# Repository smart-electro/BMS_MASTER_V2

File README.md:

BMS_MASTER_V2
=============

SW and HW for master module of battery management system

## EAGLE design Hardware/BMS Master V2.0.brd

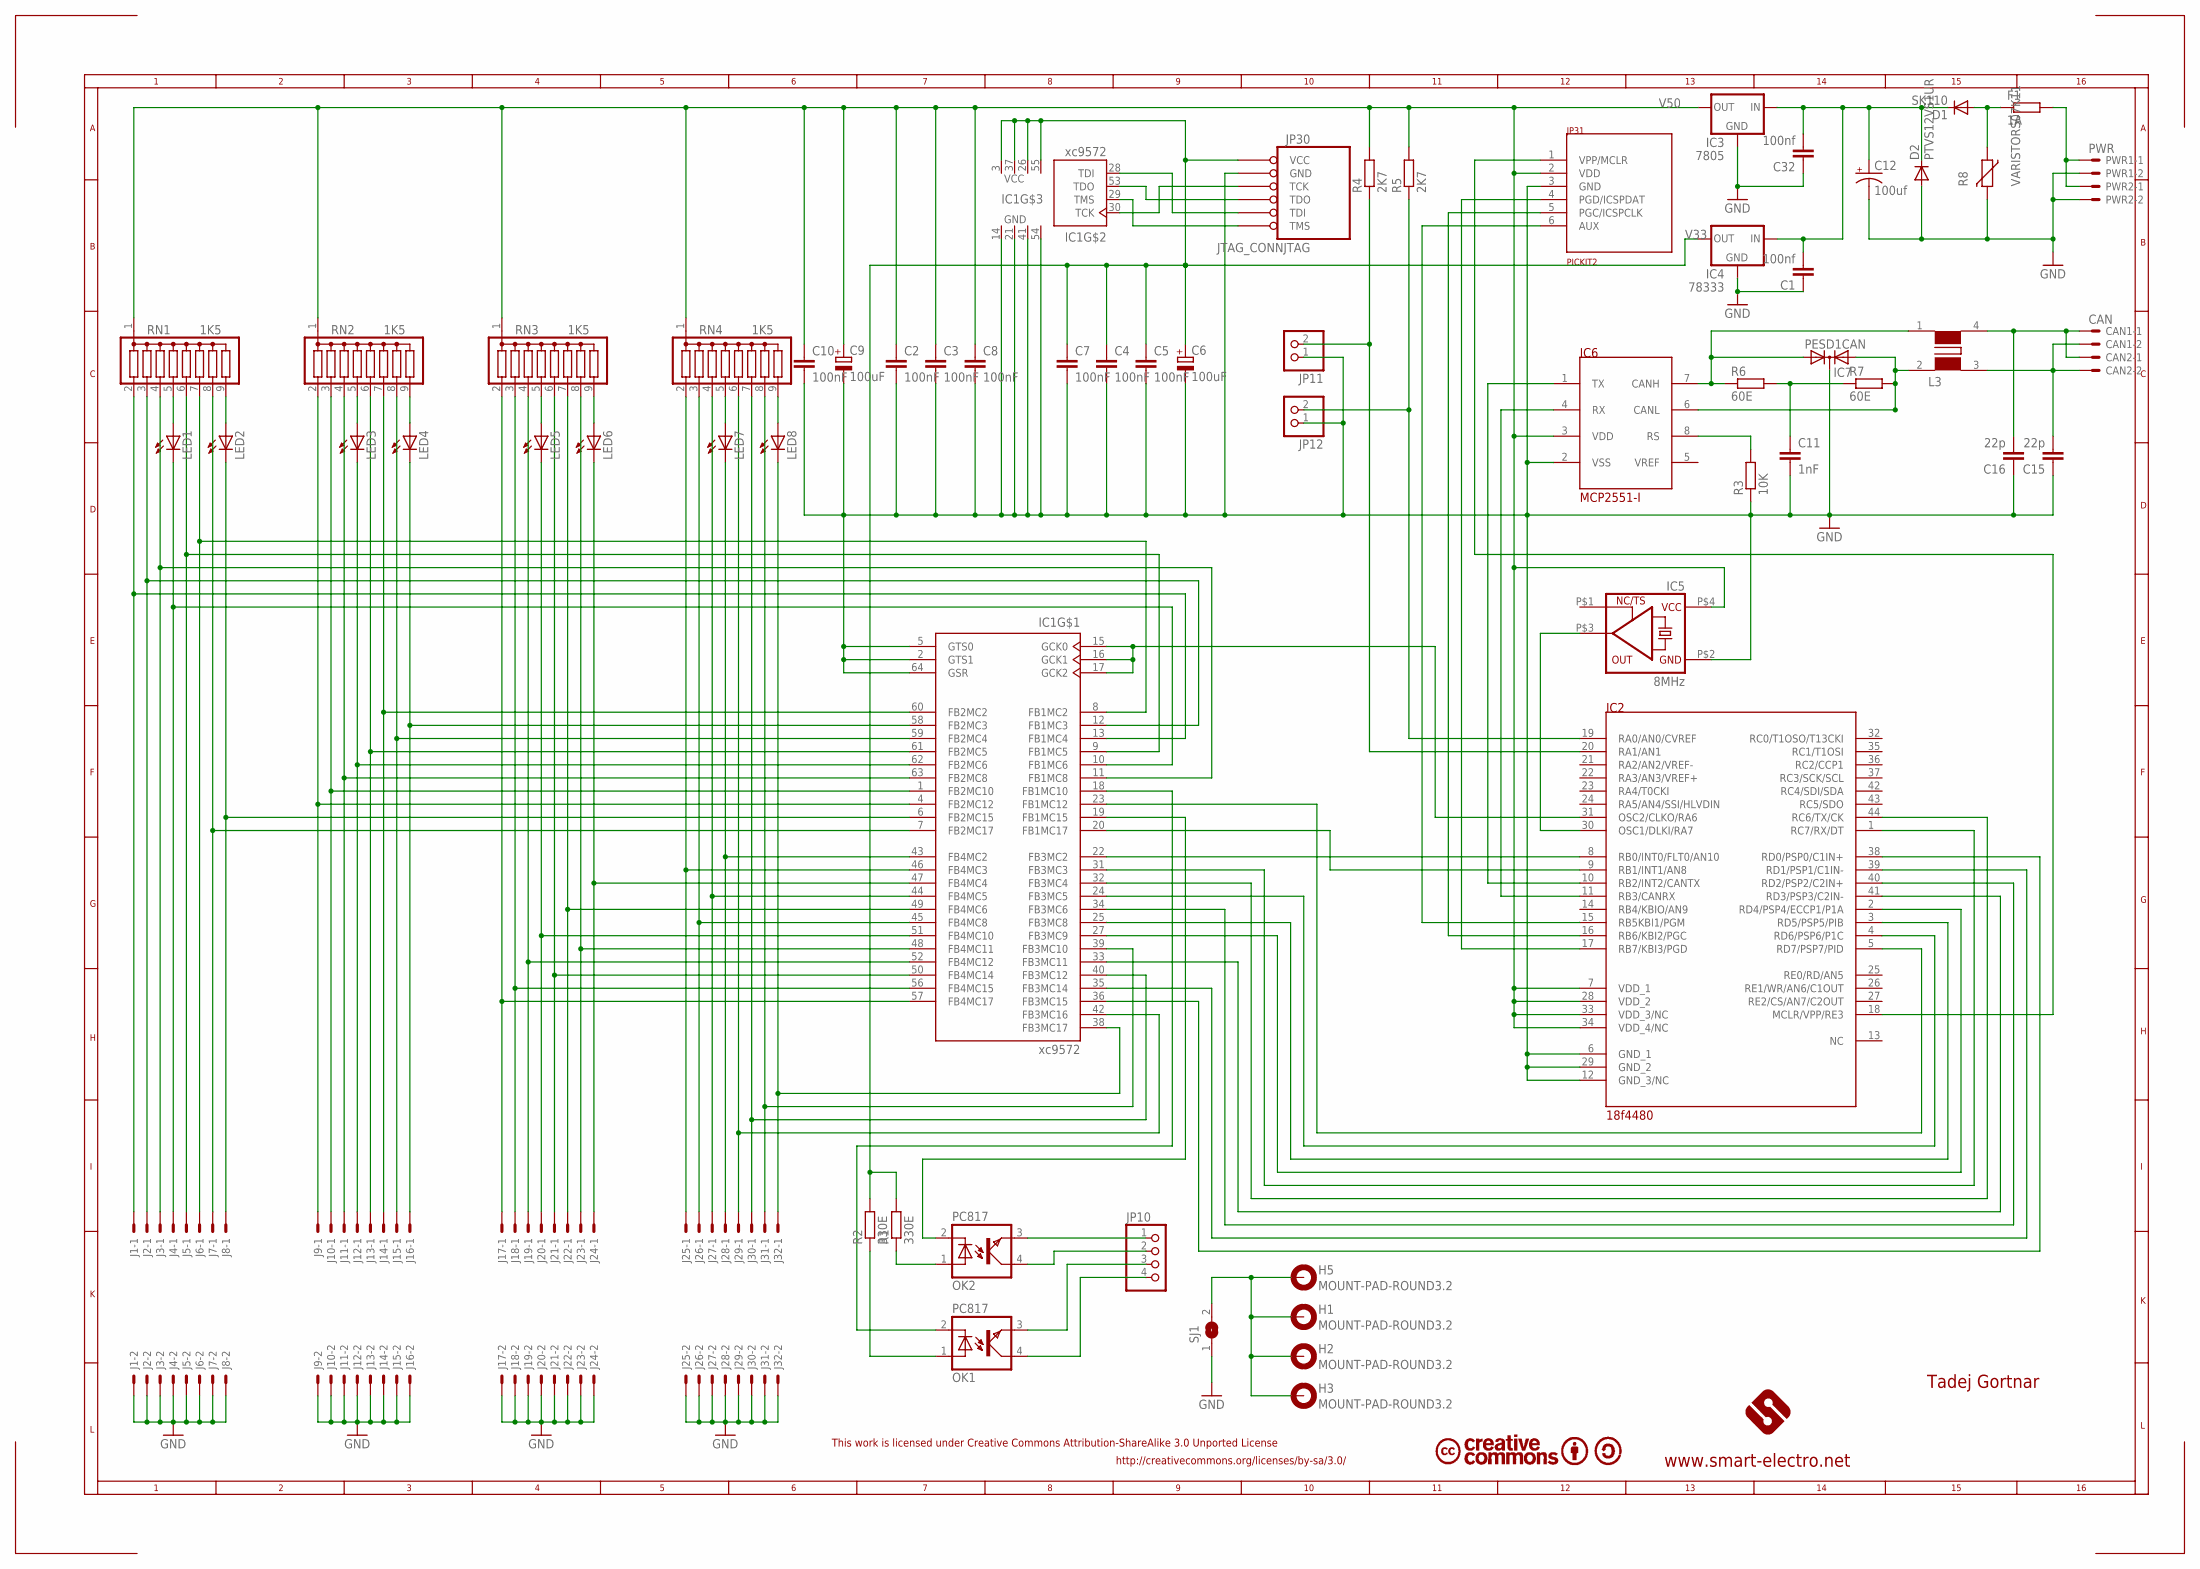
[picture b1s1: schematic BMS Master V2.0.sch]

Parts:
C1, C32: 100nf; C0805
C2, C3, C4, C5, C7, C8, C10: 100nF; C0805
C6, C9: 100uF; E2,5-5
C11: 1nF; C0805
C12: 100uf; PANASONIC_C
C15, C16: 22p; C0805
CAN1, CAN2: CAN; 6410-02
D1: SK110; MINIMELF
D2: PTVS12VS1UR; SOD323-W
F1: 1A; R1206
H1, H2, H3, H5: MOUNT-PAD-ROUND3.2; 3,2-PAD
IC1: xc9572; VQ64
IC2: 18f4480; TQFP44
IC3: 7805; SOT223
IC4: 78333; SOT223
IC5: 8MHz; CSX750
IC6: MCP2551-I; SO-08
IC7: PESD1CAN; SOT23
J1, J2, J3, J4, J5, J6, J7, J8, J9, J10, J11, J12, J13, J14, J15, J16, J17, J18, J19, J20, J21, J22, J23, J24, J25, J26, J27, J28, J29, J30, J31, J32: 22-27-2021-02; 6410-02
JP10: PINHD-1X4; 1X04
JP11, JP12: PINHD-1X2; 1X02
JP30: JTAG_CONNJTAG; PIN06
JP31: PICKIT2; PINHD-1X6
L3: WE-DD_M/S
LED1, LED2, LED3, LED4, LED5, LED6, LED7, LED8: LEDCHIPLED_0805; CHIPLED_0805
OK1, OK2: PC817; DIL04
PWR1, PWR2: PWR; 6410-02
R1, R2: 330E; M0805
R3: 10K; M0805
R4, R5: 2K7; M0805
R6, R7: 60E; R0805
R8: VARISTORS07K11; S07K11
RN1, RN2, RN3, RN4: 1K5; SIL9
SJ1: SJ

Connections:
AGND: H1.B3,2, H2.B3,2, H3.B3,2, H5.B3,2, SJ1.2
GND: C1.1, C2.2, C3.2, C4.2, C5.2, C6.-, C7.2, C8.2, C9.-, C10.2, C11.2, C12.-, C15.1, C16.1, C32.1, D2.A, IC1.2 (GTS1), IC1.5 (GTS0), IC1.14 (GND), IC1.21 (GND), IC1.41 (GND), IC1.54 (GND), IC1.64 (GSR), IC2.6 (GND_1), IC2.12 (GND_3/NC), IC2.29 (GND_2), IC3.2 (GND), IC4.2 (GND), IC5.P$2 (GND), IC6.2 (VSS), IC7.3 (C), J1.2, J2.2, J3.2, J4.2, J5.2, J6.2, J7.2, J8.2, J9.2, J10.2, J11.2, J12.2, J13.2, J14.2, J15.2, J16.2, J17.2, J18.2, J19.2, J20.2, J21.2, J22.2, J23.2, J24.2, J25.2, J26.2, J27.2, J28.2, J29.2, J30.2, J31.2, J32.2, JP11.1, JP12.1, JP30.2 (GND), JP31.3 (GND), PWR1.2, PWR2.2, R3.1, R8.2, SJ1.1
unnamed: IC1.23 (FB1MC12), IC2.5 (RD7/PSP7/PID)
unnamed: IC1.9 (FB1MC5), J5.1, RN1.6
unnamed: IC1.8 (FB1MC2), J6.1, RN1.7
unnamed: IC1.44 (FB4MC5), J27.1, RN4.4
unnamed: IC1.45 (FB4MC8), J26.1, RN4.3
unnamed: IC1.46 (FB4MC3), J25.1, RN4.2
unnamed: IC1.7 (FB2MC17), J7.1, RN1.8
unnamed: IC1.61 (FB2MC5), J13.1, RN2.6
unnamed: IC1.60 (FB2MC2), J14.1, RN2.7
unnamed: IC1.52 (FB4MC12), J19.1, RN3.4
unnamed: IC1.56 (FB4MC15), J18.1, RN3.3
unnamed: IC2.18 (MCLR/VPP/RE3), JP31.1 (VPP/MCLR)
unnamed: IC1.59 (FB2MC4), J15.1, RN2.8
unnamed: IC1.50 (FB4MC14), J21.1, RN3.6
unnamed: IC1.49 (FB4MC6), J22.1, RN3.7
unnamed: IC1.63 (FB2MC8), J11.1, RN2.4
unnamed: IC1.1 (FB2MC10), J10.1, RN2.3
unnamed: IC1.4 (FB2MC12), J9.1, RN2.2
unnamed: IC1.48 (FB4MC11), J23.1, RN3.8
unnamed: IC1.42 (FB3MC16), J29.1, RN4.6
unnamed: IC1.40 (FB3MC12), J30.1, RN4.7
unnamed: IC1.11 (FB1MC8), J3.1, RN1.4
unnamed: IC1.12 (FB1MC3), J2.1, RN1.3
unnamed: IC1.13 (FB1MC4), J1.1, RN1.2
unnamed: IC2.17 (RB7/KBI3/PGD), JP31.4 (PGD/ICSPDAT)
unnamed: IC2.16 (RB6/KBI2/PGC), JP31.5 (PGC/ICSPCLK)
unnamed: IC2.10 (RB2/INT2/CANTX), IC6.1 (TX)
unnamed: IC2.11 (RB3/CANRX), IC6.4 (RX)
unnamed: C11.1, R6.2, R7.1
unnamed: IC6.7 (CANH), IC7.1 (A1), L3.1 (2), R6.1
unnamed: IC2.30 (OSC1/DLKI/RA7), IC5.P$3 (OUT)
unnamed: C1.2, C12.+, C32.2, D1.C, D2.C, IC3.1 (IN), IC4.1 (IN)
unnamed: IC1.15 (GCK0), IC1.16 (GCK1), IC1.17 (GCK2), IC2.31 (OSC2/CLKO/RA6)
unnamed: IC1.57 (FB4MC17), J17.1, RN3.2
unnamed: IC1.38 (FB3MC17), J32.1, LED8.C
unnamed: IC1.36 (FB3MC15), IC2.38 (RD0/PSP0/C1IN+)
unnamed: IC1.35 (FB3MC14), IC2.39 (RD1/PSP1/C1IN-)
unnamed: IC1.34 (FB3MC6), IC2.40 (RD2/PSP2/C2IN+)
unnamed: IC1.33 (FB3MC11), IC2.41 (RD3/PSP3/C2IN-)
unnamed: IC1.32 (FB3MC4), IC2.44 (RC6/TX/CK)
unnamed: IC1.31 (FB3MC3), IC2.1 (RC7/RX/DT)
unnamed: IC1.27 (FB3MC9), IC2.2 (RD4/PSP4/ECCP1/P1A)
unnamed: IC1.19 (FB1MC15), OK2.2 (C)
unnamed: IC1.18 (FB1MC10), OK1.2 (C)
unnamed: OK1.1 (A), R2.1
unnamed: OK2.1 (A), R1.1
unnamed: JP10.4, OK1.4 (COL)
unnamed: JP10.3, OK1.3 (EMIT)
unnamed: JP10.2, OK2.4 (COL)
unnamed: JP10.1, OK2.3 (EMIT)
unnamed: LED1.A, RN1.5
unnamed: IC1.39 (FB3MC10), J31.1, RN4.8
unnamed: LED3.A, RN2.5
unnamed: LED2.A, RN1.9
unnamed: LED5.A, RN3.5
unnamed: LED4.A, RN2.9
unnamed: LED7.A, RN4.5
unnamed: LED6.A, RN3.9
unnamed: IC1.10 (FB1MC6), J4.1, LED1.C
unnamed: LED8.A, RN4.9
unnamed: IC1.58 (FB2MC3), J16.1, LED4.C
unnamed: IC1.51 (FB4MC10), J20.1, LED5.C
unnamed: IC1.6 (FB2MC15), J8.1, LED2.C
unnamed: IC1.62 (FB2MC6), J12.1, LED3.C
unnamed: IC1.47 (FB4MC4), J24.1, LED6.C
unnamed: IC1.43 (FB4MC2), J28.1, LED7.C
unnamed: IC1.25 (FB3MC8), IC2.3 (RD5/PSP5/PIB)
unnamed: IC1.24 (FB3MC5), IC2.4 (RD6/PSP6/P1C)
unnamed: IC6.8 (RS), R3.2
unnamed: IC2.19 (RA0/AN0/CVREF), JP12.2, R5.1
unnamed: IC2.20 (RA1/AN1), JP11.2, R4.1
unnamed: IC2.15 (RB5KBI1/PGM), JP31.6 (AUX)
unnamed: IC1.20 (FB1MC17), IC2.9 (RB1/INT1/AN8)
unnamed: IC1.22 (FB3MC2), IC2.8 (RB0/INT0/FLT0/AN10)
unnamed: IC6.6 (CANL), IC7.2 (A2), L3.2 (1), R7.2
unnamed: F1.2, PWR1.1, PWR2.1
unnamed: D1.A, F1.1, R8.1
unnamed: C16.2, CAN1.1, CAN2.1, L3.4 (3)
unnamed: C15.2, CAN1.2, CAN2.2, L3.3 (4)
TCK: IC1.30 (TCK), JP30.3 (TCK)
TDI: IC1.28 (TDI), JP30.5 (TDI)
TDO: IC1.53 (TDO), JP30.4 (TDO)
TMS: IC1.29 (TMS), JP30.6 (TMS)
V33: C4.1, C5.1, C6.+, C7.1, IC1.3 (VCC), IC1.26 (VCC), IC1.37 (VCC), IC1.55 (VCC), IC4.3 (OUT), JP30.1 (VCC), R1.2, R2.2
V50: C2.1, C3.1, C8.1, C9.+, C10.1, IC2.7 (VDD_1), IC2.28 (VDD_2), IC2.33 (VDD_3/NC), IC2.34 (VDD_4/NC), IC3.3 (OUT), IC5.P$4 (VCC), IC6.3 (VDD), JP31.2 (VDD), R4.2, R5.2, RN1.1, RN2.1, RN3.1, RN4.1

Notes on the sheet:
http://creativecommons.org/licenses/by-sa/3.0/
This work is licensed under Creative Commons Attribution-ShareAlike 3.0 Unported License
www.smart-electro.net
Tadej Gortnar

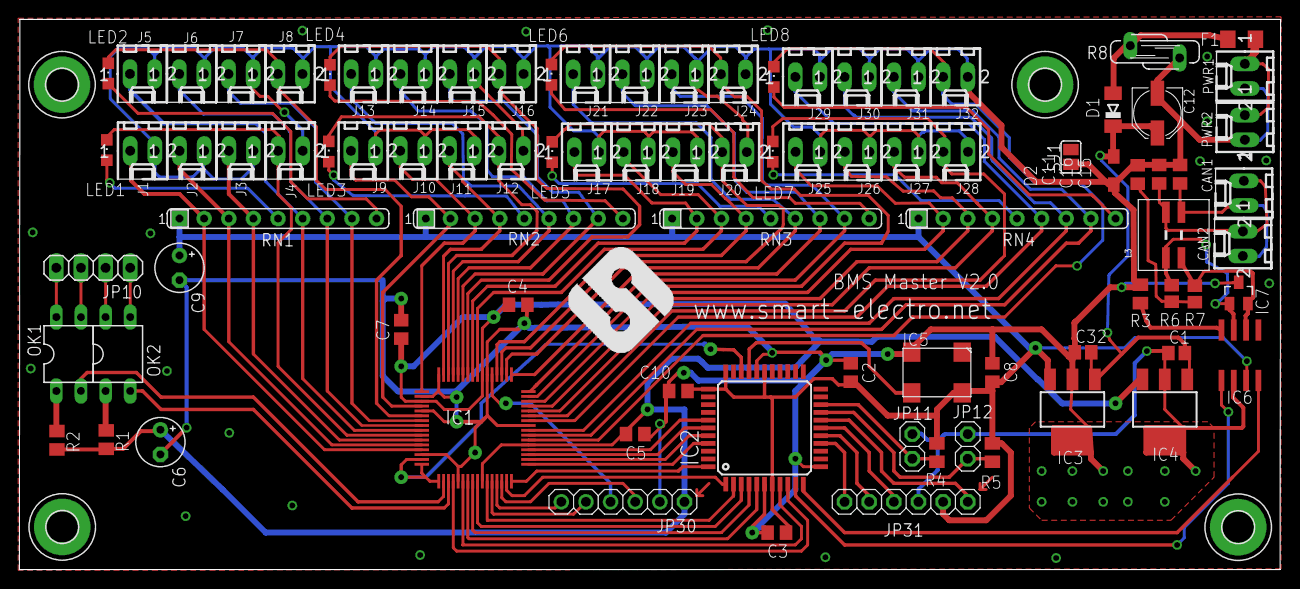
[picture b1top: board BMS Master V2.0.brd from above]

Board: 2 copper layers, 130.1 x 56.7 mm, 94 parts (0 on the bottom side), 87 nets.

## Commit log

2014-06-29 initial comit
2016-07-19 Added TC charger app
2016-07-19 unknown.
2016-07-19 unknown
